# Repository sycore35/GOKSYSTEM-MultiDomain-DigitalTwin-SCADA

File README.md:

<div align="center">

# GÖKSYSTEM 3.0

**Industrial SCADA and 3D digital twin of a small plant: a 10 Hz physics simulation, ISA-18.2 alarm handling,
a PLC ladder runtime, and a KiCad-designed field card for every asset.**

</div>

GÖKSYSTEM simulates four plant areas — a production line, a chemical process loop, an 11 kV substation and a
building with solar and battery storage — and runs them the way a real control system would: field sensors and
actuators are wired to PLC cards, the cards talk Modbus to a SCADA server, and operators work from an HMI with
alarms, trends, an audit trail and a 3D twin that moves with the live data. The operator interface is in Turkish.

## Highlights

- **Physics at 10 Hz** — conveyor with VFD and emergency braking, transformer thermal model with ANSI 49/50
  protection, tank level (Torricelli) with a PID pH loop, building HVAC with PV and battery. Fixed seed and
  scheduled fault scenarios make every run reproducible. Equations are in [`docs/ENGINEERING_MODELS.md`](docs/ENGINEERING_MODELS.md).
- **Live 3D twin** — products move at the measured belt speed, the robot follows its joint angles, the tank fills
  to the measured level, the valve stem tracks its position, breaker contacts open on a trip and transformer fans
  start with oil temperature. Click any machine for live values, alarms, trend, health score and run history.
- **A field card per asset** — 12 GK-P1 PLC cards and 3 GK-S1 smart retrofit cards, each a separate KiCad 10
  design (0 DRC errors), each running its own ladder program every tick. See [`hardware/`](hardware/README.md).
- **Communication diagram** — Purdue-style view from sensors to historian, with the real protocol written on every link.
- **Alarm management** — ISA-18.2 state machine (unacknowledged, acknowledged, return-to-normal, shelved) with
  priorities, deadband, shelving with reason and a full transition history.
- **Protocols** — Modbus TCP server, MQTT topics, an OPC UA node model and a Factory I/O bridge.
- **Measured, not assumed** — tick jitter, overruns, fault isolation and determinism are profiled in the app and
  documented in [`docs/TIMING.md`](docs/TIMING.md).

## Screenshots

| Production line | Process loop |
|:---:|:---:|
|  |  |
| **Substation** | **Click-to-inspect** |
|  |  |
| **Alarm center during a fault scenario** | **Plant overview** |
|  |  |

### Communication diagram

### Field cards

<table>
<tr>
<td></td>
<td></td>
</tr>
<tr>
<td align="center"><b>GK-P1-11</b> · motor PLC card — 3 DI, 2 × 4–20 mA, 3 MOSFET outputs, RS-485</td>
<td align="center"><b>GK-S1-41</b> · HVAC smart card — I²C climate sensor, CO₂ loop input, RS-485</td>
</tr>
</table>

## Architecture

```mermaid
flowchart TB
  subgraph L3[Level 3 · Records]
    HIST[(Historian<br/>SQLite WAL)]
    AUD[Audit trail<br/>SHA-256 chain]
  end
  subgraph L2[Level 2 · Control and monitoring]
    HMI[Operator HMI<br/>React + Three.js]
    SCADA[SCADA server<br/>FastAPI · 10 Hz loop]
    GW[Protocol gateways<br/>Modbus TCP · MQTT · OPC UA]
  end
  subgraph L1[Level 1 · Field cards]
    PLC[GK-P1 PLC cards × 12<br/>ladder program per asset]
    SMART[GK-S1 smart cards × 3]
  end
  subgraph L0[Level 0 · Plant]
    DEV[12 machines<br/>conveyor · robot · motor · tank · pump · valve<br/>transformer · breaker · busbar · HVAC · PV · battery]
  end
  HMI <-- "HTTP · WebSocket 100 ms" --> SCADA
  SCADA --> HIST
  SCADA --> AUD
  SCADA <--> GW
  SCADA <-- "Modbus RTU over RS-485" --> PLC
  SMART -- "RS-485" --> PLC
  PLC <-- "4–20 mA · 24 V I/O" --> DEV
  SMART <-- "I²C" --> DEV
```

| Protocol | Where | Details |
|---|---|---|
| HTTP REST | HMI ⇄ SCADA server | `/api/v1`, OpenAPI docs at `/docs` |
| WebSocket | SCADA server → HMI | `/ws`, changed points every 100 ms |
| Modbus TCP | protocol simulator, Factory I/O bridge | real server on `127.0.0.1:5020`, writes disabled by default |
| MQTT | SCADA → external systems | `goksystem/telemetry/{area}/{device}/{point}`; in-memory bus when no broker is reachable |
| OPC UA | SCADA → external systems | node model `ns=2;s=GOKSYSTEM.*` (not a network server yet) |
| Modbus RTU | gateways ⇄ cards, cards ⇄ drives / analyzers / BMS | RS-485, 19200 8E1 |
| 4–20 mA, 24 V I/O, I²C | sensors and actuators ⇄ cards | NAMUR NE 43 limits, opto inputs, MOSFET outputs |

More detail in [`docs/ARCHITECTURE.md`](docs/ARCHITECTURE.md) and [`docs/PROTOCOLS.md`](docs/PROTOCOLS.md).

## Getting started

Requires Python 3.10+ and Node.js 18+.

```bash
python3 -m venv .venv
.venv/bin/pip install -r requirements.txt
.venv/bin/python -m uvicorn goksystem.main:app --host 127.0.0.1 --port 8000
```

In a second terminal:

```bash
cd frontend
npm install
npm run dev
```

Open http://localhost:3000. Vite proxies `/api` and `/ws` to port 8000.

One-step launchers: `Start-macOS.command` (double-click; builds the UI when needed and serves everything on
port 8000), `start.sh` on Linux and `start.bat` on Windows.

| Variable | Purpose |
|---|---|
| `GOKSYSTEM_DATA_DIR` | where databases are written (default `data/`) |
| `GOKSYSTEM_SEED`, `GOKSYSTEM_NOISE_PCT` | random seed and measurement noise for reproducible runs |
| `GOKSYSTEM_AUTH_REQUIRED` | `1` to require operator login for every change |
| `GOKSYSTEM_MODBUS_SIM_PORT` | Modbus TCP port (default 5020) |
| `GOKSYSTEM_FACTORYIO_MODE` | `mock`, `live` or `off` |
| `GOKSYSTEM_PORT` | port used by the macOS launcher (default 8000) |

## Tests

```bash
.venv/bin/python -m pytest tests          # 105 tests: physics, alarms, protocols, API, PLC, field cards
cd frontend && npx tsc --noEmit && npm run build
```

GitHub Actions runs both on every push and pull request. The wall-clock timing test is skipped on shared CI
runners; run `scripts/measure_tick.py` or `scripts/measure_tick_under_load.py` locally for real numbers.

## Project layout

```
goksystem/
  core/        simulation engine, state container, device registry
  domains/     factory, process, grid and building models
  scada/       alarm engine, security
  historian/   SQLite storage
  protocols/   Modbus TCP, MQTT, OPC UA, Factory I/O
  modules/     PLC runtime, field cards, run history, energy, maintenance, scenarios, ...
  api/         REST routes and WebSocket hub
frontend/      React + Vite + Three.js operator interface
hardware/      KiCad sources of the 15 field cards and the scripts that generate them
docs/          models, architecture, protocols, timing
tests/         pytest suite
desktop/       Electron wrapper; packaging/ holds the PyInstaller entry point
```

## Notes

- This is a simulator for learning and demonstration, not a certified control or safety system. The field cards
  are complete KiCad designs but have not been manufactured or bench-tested.
- Everything binds to localhost; authentication is off unless `GOKSYSTEM_AUTH_REQUIRED=1`.
- The 3D scene is built from procedural meshes; see [`ASSET_CREDITS.md`](ASSET_CREDITS.md).
- Desktop installers are built by `.github/workflows/desktop-packaging.yml` on version tags.

## Author

**Ömer İşcan** — [LinkedIn](https://www.linkedin.com/in/%C3%B6mer-i%C5%9Fcan-9a64b52b6/) · [GitHub](https://github.com/sycore35)

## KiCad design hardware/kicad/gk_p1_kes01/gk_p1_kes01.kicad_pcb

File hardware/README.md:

# Field cards: GK-P1 (PLC) and GK-S1 (smart retrofit)

Every asset in the plant has its own **GK-P1 PLC card**. The motor, the feed pump and the HVAC unit also have a
**GK-S1 smart retrofit card** for condition-monitoring sensors. That is 15 KiCad designs, one per card.

| Card | MCU | I/O | Bus |
|---|---|---|---|
| GK-P1 | ESP32-S3-WROOM-1 | only the blocks the asset uses: up to 4 × 24 V opto DI, 2 × 4–20 mA AI, 4 × MOSFET DO | RS-485 Modbus RTU |
| GK-S1 | ESP32-S3-WROOM-1 | I²C sensor header (ADXL355, SHT31) and the 4–20 mA inputs it needs | RS-485 Modbus RTU |

Both are 2-layer boards with a protected 24 V input (fuse, reverse-polarity Schottky, SMAJ28A TVS, R-78B3.3
DC/DC). All 15 pass DRC with 0 errors and 0 unrouted connections under JLCPCB's 2-layer limits
(0.2 mm minimum hole, 0.3 mm copper-to-edge).

## Where things are

| Path | Contents |
|---|---|
| `hardware/kicad/<card>/` | editable KiCad project (`.kicad_pro/.kicad_sch/.kicad_pcb`), Gerber zip, BOM, pick-and-place, DRC/ERC reports |
| `frontend/public/boards/<card>/` | 3D renders, schematic PDF, BOM and DRC summary shown on the *Saha Kartları* page and in the 3D twin |
| `goksystem/modules/hardware.py` | wiring of every card: terminals, sensors, Modbus address, ladder program |

Open `hardware/kicad/<card>/<card>.kicad_pro` in KiCad 10. The library tables point at the default macOS
install (`/Applications/KiCad`); on other systems re-point them in *Preferences → Manage Libraries*.

## How the designs are generated

1. `make_gk_n1_spec.py` builds **GK-N1**, the full-option base: an existing routed retrofit-node design with
   its stacking header replaced by an I²C header and four low-side MOSFET outputs added on the free GPIOs.
2. `make_card_specs.py` derives each card from GK-N1 by removing the channel blocks the asset does not use.
   Parts are only removed, never moved, so the placement stays the proven one.
3. `build_all_cards.py` runs the KiCad pipeline (schematic, placement, FreeRouting, DRC, Gerbers) for every
   card and retries a card when the autorouter stops with open connections.
4. `finish_card.py` adds the silkscreen label (card id, asset, Modbus address), applies the fab limits,
   re-runs DRC, re-exports Gerbers and renders, and copies the results to the two folders above.

```bash
export GOKSYSTEM_EDA_DIR=/path/to/pipeline/workspace   # folder with specs/ and projects/
.venv/bin/python hardware/build_all_cards.py --jobs 3   # all 15 cards
.venv/bin/python hardware/build_all_cards.py gk_p1_tnk01
```

## Limits

- The output column of GK-N1 was placed by hand; everything else follows the base design. Silkscreen overlap
  warnings remain (cosmetic), and unused ESP32 pins show up as schematic-parity warnings.
- Analog outputs are not on the card: the valve positioner and drives are reached over RS-485.
- In the simulation the card outputs only drive relay states; they never command the plant.
- The boards have not been manufactured or bench-tested.

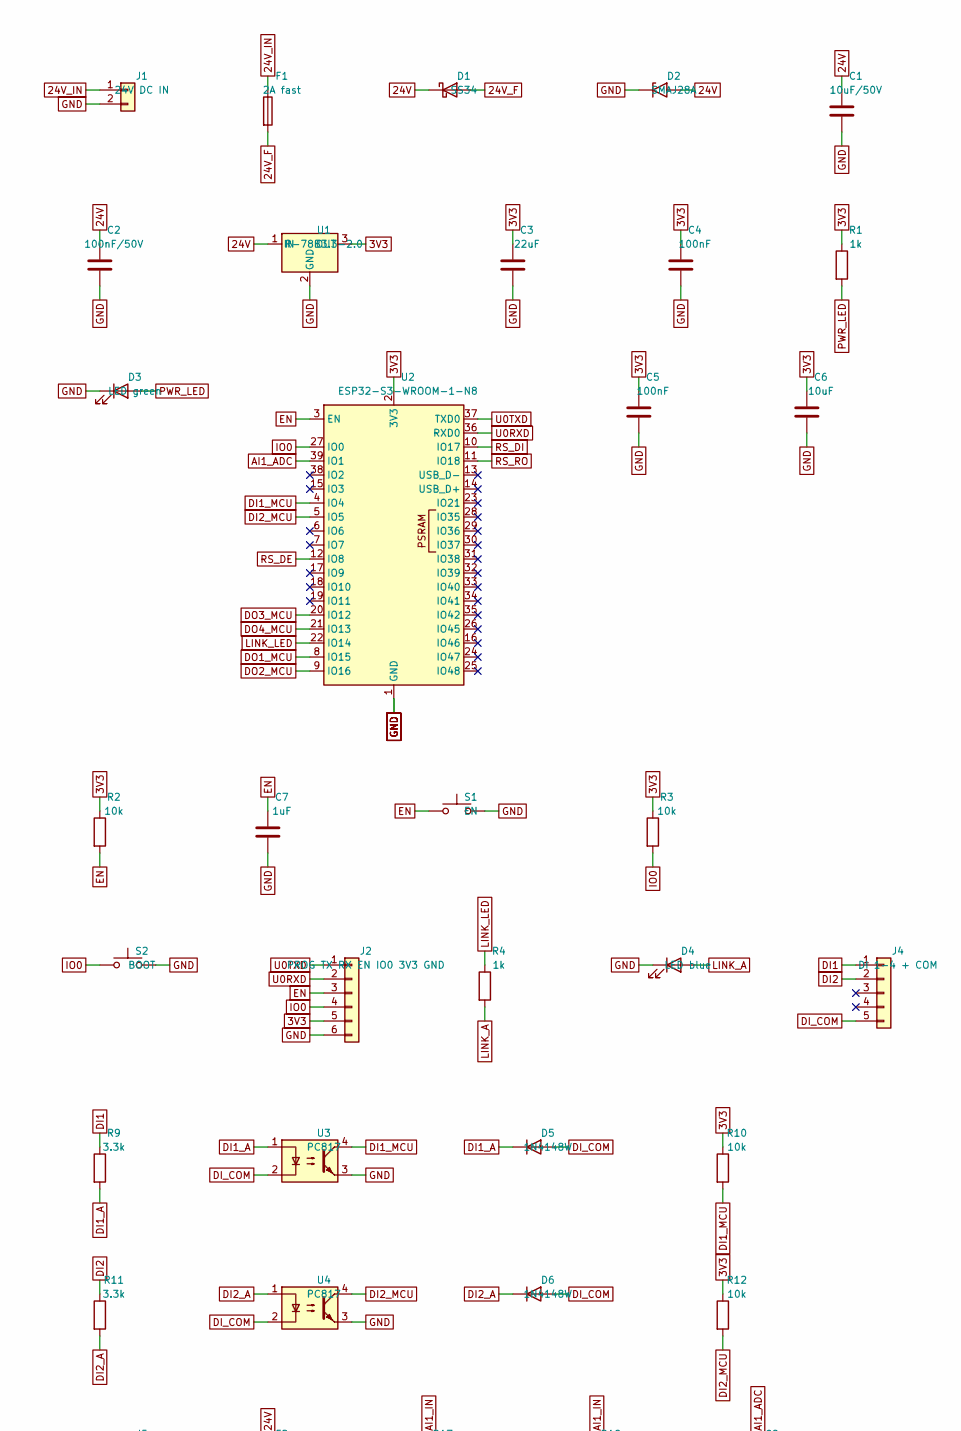
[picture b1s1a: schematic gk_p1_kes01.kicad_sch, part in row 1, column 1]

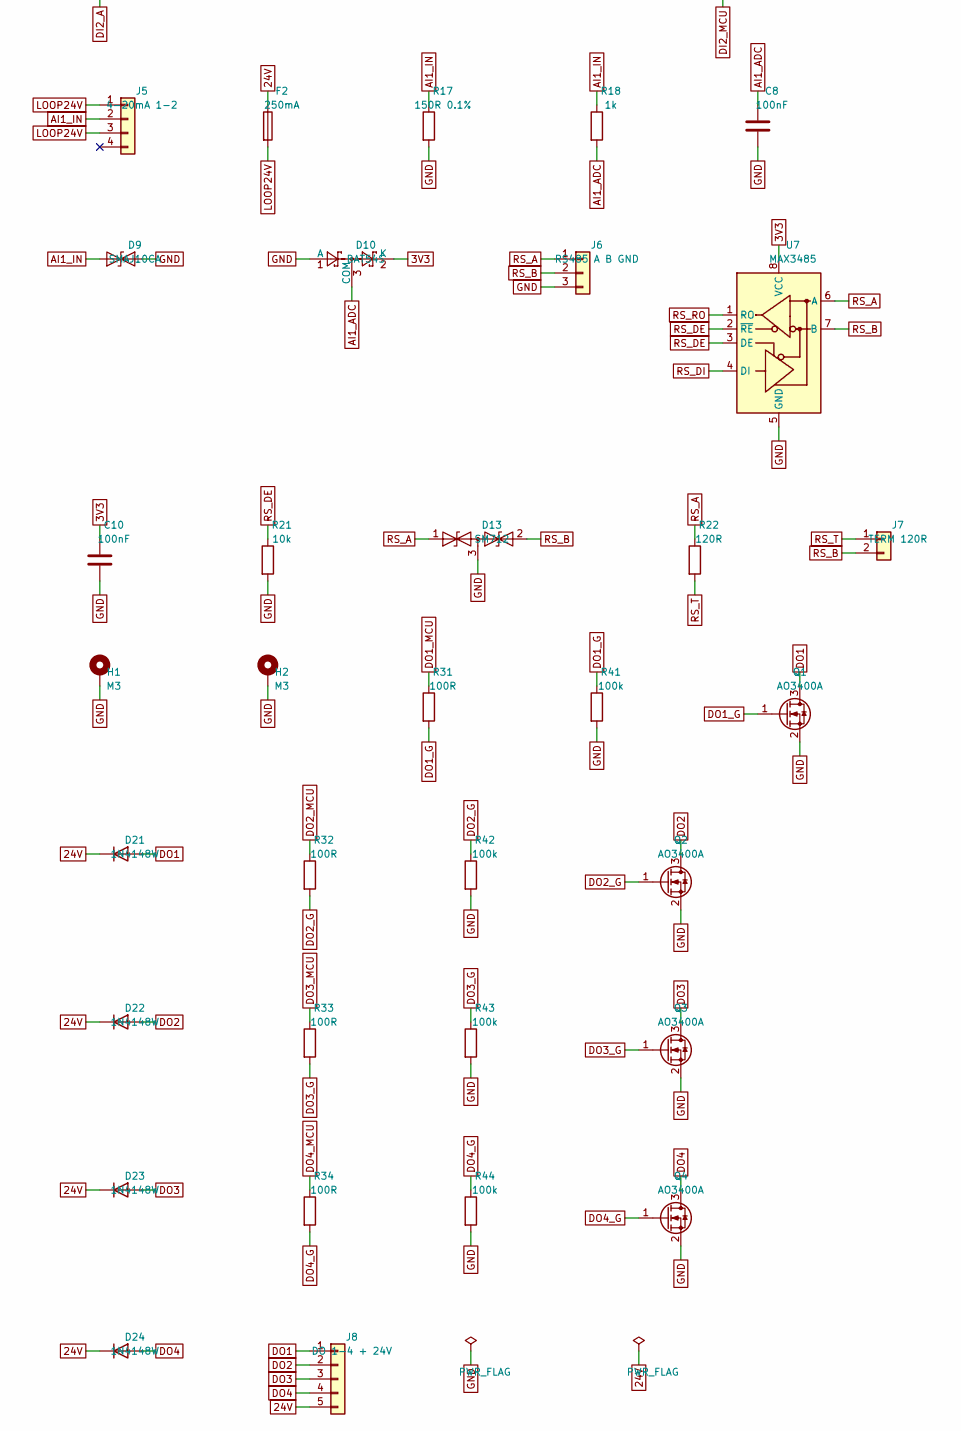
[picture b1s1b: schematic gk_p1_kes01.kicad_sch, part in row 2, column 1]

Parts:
C1: 10uF/50V; C_1210_3225Metric
C2: 100nF/50V; C_0603_1608Metric
C3: 22uF; C_0805_2012Metric
C4, C5, C8, C10: 100nF; C_0603_1608Metric
C6: 10uF; C_0805_2012Metric
C7: 1uF; C_0603_1608Metric
D1: SS34; D_SMA
D2: SMAJ28A; D_SMA
D3: LED green; LED_0603_1608Metric
D4: LED blue; LED_0603_1608Metric
D5, D6, D21, D22, D23, D24: 1N4148W; D_SOD-123
D9: SMAJ10CA; D_SMA
D10: BAT54S; SOT-23
D13: SM712; SOT-23
F1: 2A fast; Fuse_1206_3216Metric
F2: 250mA; Fuse_1206_3216Metric
H1, H2: M3; MountingHole_3.2mm_M3_Pad
J1: 24V DC IN; PhoenixContact_MSTBA_2,5_2-G-5,08_1x02_P5.08mm_Horizontal
J2: PROG TX RX EN IO0 3V3 GND; PinHeader_1x06_P2.54mm_Vertical
J4: DI 1-4 + COM; PhoenixContact_MC_1,5_5-G-3.5_1x05_P3.50mm_Horizontal
J5: 4-20mA 1-2; PhoenixContact_MC_1,5_4-G-3.5_1x04_P3.50mm_Horizontal
J6: RS485 A B GND; PhoenixContact_MC_1,5_3-G-3.5_1x03_P3.50mm_Horizontal
J7: TERM 120R; PinHeader_1x02_P2.54mm_Vertical
J8: DO 1-4 + 24V; PhoenixContact_MC_1,5_5-G-3.5_1x05_P3.50mm_Horizontal
Q1, Q2, Q3, Q4: AO3400A; SOT-23
R1, R4, R18: 1k; R_0603_1608Metric
R2, R3, R10, R12, R21: 10k; R_0603_1608Metric
R9, R11: 3.3k; R_1206_3216Metric
R17: 150R 0.1%; R_0603_1608Metric
R22: 120R; R_0603_1608Metric
R31, R32, R33, R34: 100R; R_0603_1608Metric
R41, R42, R43, R44: 100k; R_0603_1608Metric
S1: EN; SW_SPST_TL3342
S2: BOOT; SW_SPST_TL3342
U1: R-78B3.3-2.0; Converter_DCDC_RECOM_R-78B-2.0_THT
U2: ESP32-S3-WROOM-1-N8; ESP32-S3-WROOM-1
U3, U4: PC817; SOP-4_7.5x4.1mm_P2.54mm
U7: MAX3485; SOIC-8_3.9x4.9mm_P1.27mm

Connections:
3V3: C3.1, C4.1, C5.1, C6.1, C10.1, D10.2 (K), J2.5, R1.1, R2.1, R3.1, R10.1, R12.1, U1.3 (OUT), U2.2 (3V3), U7.8 (VCC)
24V: C1.1, C2.1, D1.1 (K), D2.2 (A2), D21.1 (K), D22.1 (K), D23.1 (K), D24.1 (K), F2.1, J8.5, U1.1 (IN)
24V_F: D1.2 (A), F1.2
24V_IN: F1.1, J1.1
AI1_ADC: C8.1, D10.3 (COM), R18.2, U2.39 (IO1)
AI1_IN: D9.1 (A1), J5.2, R17.1, R18.1
DI1: J4.1, R9.1
DI1_A: D5.1 (K), R9.2, U3.1
DI1_MCU: R10.2, U2.4 (IO4), U3.4
DI2: J4.2, R11.1
DI2_A: D6.1 (K), R11.2, U4.1
DI2_MCU: R12.2, U2.5 (IO5), U4.4
DI_COM: D5.2 (A), D6.2 (A), J4.5, U3.2, U4.2
DO1: D21.2 (A), J8.1, Q1.3 (D)
DO1_G: Q1.1 (G), R31.2, R41.1
DO1_MCU: R31.1, U2.8 (IO15)
DO2: D22.2 (A), J8.2, Q2.3 (D)
DO2_G: Q2.1 (G), R32.2, R42.1
DO2_MCU: R32.1, U2.9 (IO16)
DO3: D23.2 (A), J8.3, Q3.3 (D)
DO3_G: Q3.1 (G), R33.2, R43.1
DO3_MCU: R33.1, U2.20 (IO12)
DO4: D24.2 (A), J8.4, Q4.3 (D)
DO4_G: Q4.1 (G), R34.2, R44.1
DO4_MCU: R34.1, U2.21 (IO13)
EN: C7.1, J2.3, R2.2, S1.1, U2.3 (EN)
GND: C1.2, C2.2, C3.2, C4.2, C5.2, C6.2, C7.2, C8.2, C10.2, D2.1 (A1), D3.1 (K), D4.1 (K), D9.2 (A2), D10.1 (A), D13.3 (common), H1.1, H2.1, J1.2, J2.6, J6.3, Q1.2 (S), Q2.2 (S), Q3.2 (S), Q4.2 (S), R17.2, R21.2, R41.2, R42.2, R43.2, R44.2, S1.2, S2.2, U1.2 (GND), U2.1 (GND), U2.40 (GND), U2.41 (GND), U3.3, U4.3, U7.5 (GND)
IO0: J2.4, R3.2, S2.1, U2.27 (IO0)
LINK_A: D4.2 (A), R4.2
LINK_LED: R4.1, U2.22 (IO14)
LOOP24V: F2.2, J5.1, J5.3
PWR_LED: D3.2 (A), R1.2
RS_A: D13.1 (A1), J6.1, R22.1, U7.6 (A)
RS_B: D13.2 (A2), J6.2, J7.2, U7.7 (B)
RS_DE: R21.1, U2.12 (IO8), U7.2 (~RE), U7.3 (DE)
RS_DI: U2.10 (IO17), U7.4 (DI)
RS_RO: U2.11 (IO18), U7.1 (RO)
RS_T: J7.1, R22.2
U0RXD: J2.2, U2.36 (RXD0)
U0TXD: J2.1, U2.37 (TXD0)

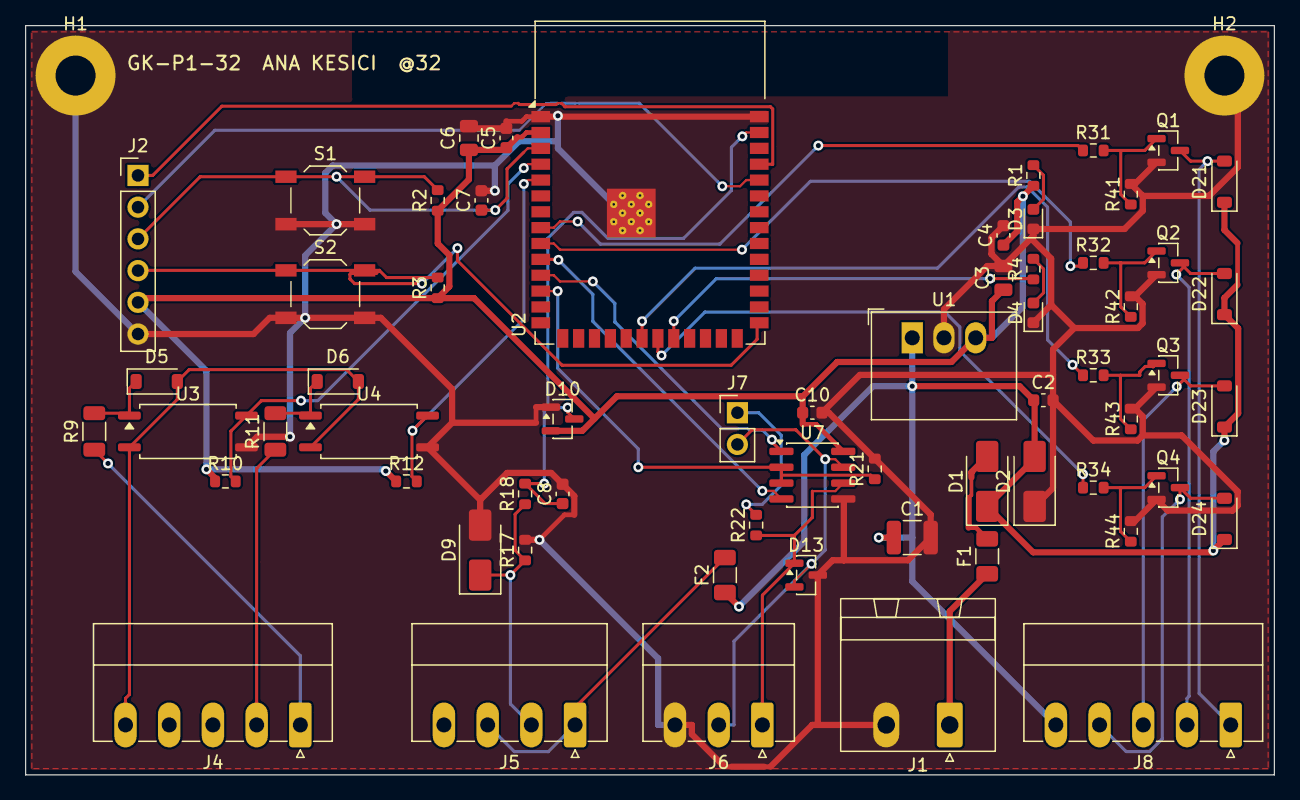
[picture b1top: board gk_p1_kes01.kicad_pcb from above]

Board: 2 copper layers, 100.0 x 60.0 mm, 64 parts (0 on the bottom side), 40 nets.

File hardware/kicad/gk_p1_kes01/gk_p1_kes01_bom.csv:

"Designator","Value","Footprint","MPN","Manufacturer","Qty"
"C1","10uF/50V","Capacitor_SMD:C_1210_3225Metric","","","1"
"C2","100nF/50V","Capacitor_SMD:C_0603_1608Metric","","","1"
"C3","22uF","Capacitor_SMD:C_0805_2012Metric","","","1"
"C4,C5,C8,C10","100nF","Capacitor_SMD:C_0603_1608Metric","","","4"
"C6","10uF","Capacitor_SMD:C_0805_2012Metric","","","1"
"C7","1uF","Capacitor_SMD:C_0603_1608Metric","","","1"
"D1","SS34","Diode_SMD:D_SMA","","","1"
"D2","SMAJ28A","Diode_SMD:D_SMA","","","1"
"D3","LED green","LED_SMD:LED_0603_1608Metric","","","1"
"D4","LED blue","LED_SMD:LED_0603_1608Metric","","","1"
"D5,D6,D21-D24","1N4148W","Diode_SMD:D_SOD-123","","","6"
"D9","SMAJ10CA","Diode_SMD:D_SMA","","","1"
"D10","BAT54S","Package_TO_SOT_SMD:SOT-23","","","1"
"D13","SM712","Package_TO_SOT_SMD:SOT-23","","","1"
"F1","2A fast","Fuse:Fuse_1206_3216Metric","","","1"
"F2","250mA","Fuse:Fuse_1206_3216Metric","","","1"
"H1,H2","M3","MountingHole:MountingHole_3.2mm_M3_Pad","","","2"
"J1","24V DC IN","Connector_Phoenix_MSTB:PhoenixContact_MSTBA_2,5_2-G-5,08_1x02_P5.08mm_Horizontal","","","1"
"J2","PROG TX RX EN IO0 3V3 GND","Connector_PinHeader_2.54mm:PinHeader_1x06_P2.54mm_Vertical","","","1"
"J4","DI 1-4 + COM","Connector_Phoenix_MC:PhoenixContact_MC_1,5_5-G-3.5_1x05_P3.50mm_Horizontal","","","1"
"J5","4-20mA 1-2","Connector_Phoenix_MC:PhoenixContact_MC_1,5_4-G-3.5_1x04_P3.50mm_Horizontal","","","1"
"J6","RS485 A B GND","Connector_Phoenix_MC:PhoenixContact_MC_1,5_3-G-3.5_1x03_P3.50mm_Horizontal","","","1"
"J7","TERM 120R","Connector_PinHeader_2.54mm:PinHeader_1x02_P2.54mm_Vertical","","","1"
"J8","DO 1-4 + 24V","Connector_Phoenix_MC:PhoenixContact_MC_1,5_5-G-3.5_1x05_P3.50mm_Horizontal","","","1"
"Q1-Q4","AO3400A","Package_TO_SOT_SMD:SOT-23","","","4"
"R1,R4,R18","1k","Resistor_SMD:R_0603_1608Metric","","","3"
"R2,R3,R10,R12,R21","10k","Resistor_SMD:R_0603_1608Metric","","","5"
"R9,R11","3.3k","Resistor_SMD:R_1206_3216Metric","","","2"
"R17","150R 0.1%","Resistor_SMD:R_0603_1608Metric","","","1"
"R22","120R","Resistor_SMD:R_0603_1608Metric","","","1"
"R31-R34","100R","Resistor_SMD:R_0603_1608Metric","","","4"
"R41-R44","100k","Resistor_SMD:R_0603_1608Metric","","","4"
"S1","EN","Button_Switch_SMD:SW_SPST_TL3342","","","1"
"S2","BOOT","Button_Switch_SMD:SW_SPST_TL3342","","","1"
"U1","R-78B3.3-2.0","Converter_DCDC:Converter_DCDC_RECOM_R-78B-2.0_THT","","","1"
"U2","ESP32-S3-WROOM-1-N8","RF_Module:ESP32-S3-WROOM-1","","","1"
"U3,U4","PC817","Package_SO:SOP-4_7.5x4.1mm_P2.54mm","","","2"
"U7","MAX3485","Package_SO:SOIC-8_3.9x4.9mm_P1.27mm","","","1"
